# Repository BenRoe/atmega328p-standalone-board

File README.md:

# 328p-Standalone-TH

Development board for the Atmega328P with USB-C connector and only through hole components.  
It's very handy to flash the bootloader on many Atmega328P IC's.

## Features

- ISP 6/10 header for bootloader flashing (recommend [USBaspLoader](https://github.com/baerwolf/USBaspLoader))
- USB-C connector (if USBaspLoader bootloader is on the Atmega328P, you can flash the firmware via USB)
- ISP activity led (MISO Pin)
- Boot/Reset switch
- [ZIF](https://en.wikipedia.org/wiki/Zero_insertion_force) socket for easy MCU swap

- [Schematic](schematic.pdf)
- [BOM](http://htmlpreview.github.io/?https://github.com/BenRoe/atmega328p-standalone-board/blob/master/bom/ibom.html)
- [Gerber files](gerber/328p-standalone-rev1.0.zip) (ready to use)

## License

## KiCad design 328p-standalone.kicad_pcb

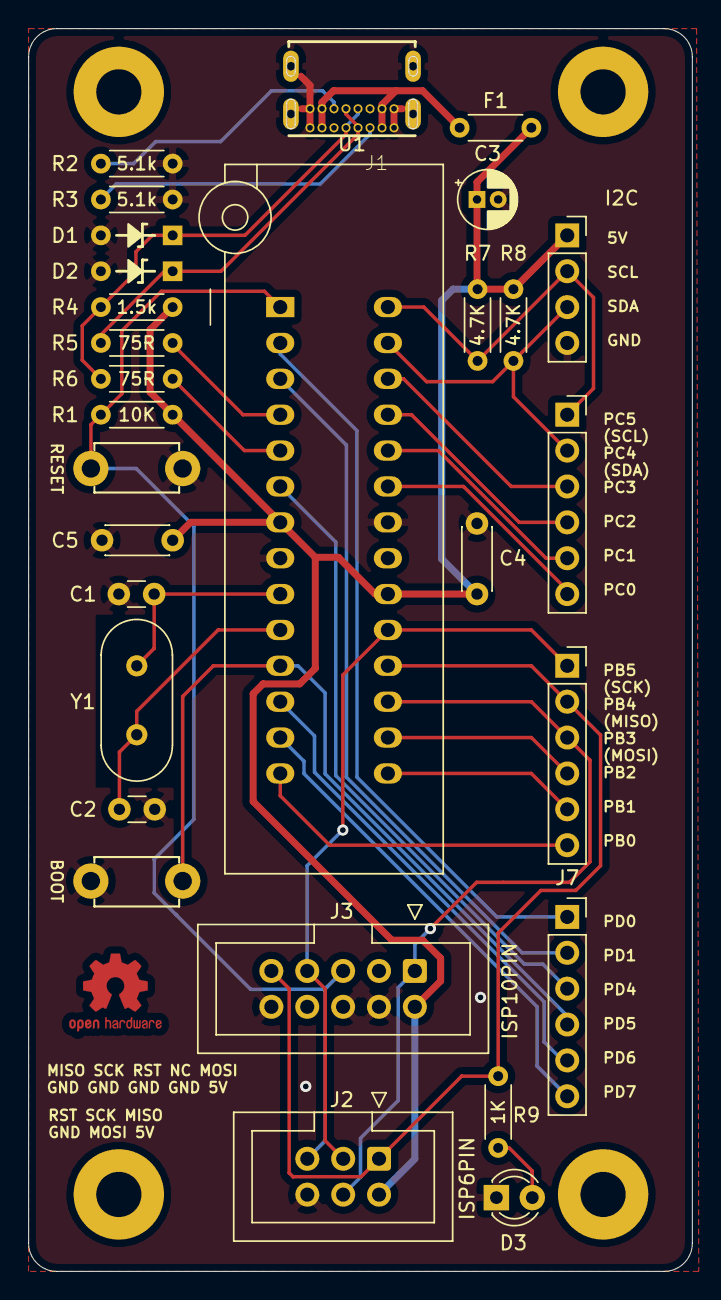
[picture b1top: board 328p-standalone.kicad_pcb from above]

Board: 2 copper layers, 47.0 x 88.0 mm, 33 parts (0 on the bottom side), 31 nets.

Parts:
C1, C2: 22pF; C_Disc_D3.0mm_W1.6mm_P2.50mm
C3: 4.7uF; CP_Radial_D4.0mm_P1.50mm
C4, C5: 100nF; C_Disc_D4.3mm_W1.9mm_P5.00mm
D1, D2: 3.6V; Diode-Zener-35_SOD27_P5.08mm_Horizontal
D3: LED; LED_D3.0mm
F1: 500mA; R_Axial_DIN0204_L3.6mm_D1.6mm_P5.08mm_Horizontal
H1, H2, H3, H4: MountingHole; MountingHole_3.2mm_M3_Pad
J1: USB4085-GF-A_REVA; GCT_USB4085-GF-A_REVA
J2: ISP6PIN; IDC-Header_2x03_P2.54mm_Vertical
J3: ISP10PIN; IDC-Header_2x05_P2.54mm_Vertical
J4: I2C; PinSocket_1x04_P2.54mm_Vertical
J5, J6, J7: Conn_01x06; PinSocket_1x06_P2.54mm_Vertical
R1: 10K; R_Axial_DIN0204_L3.6mm_D1.6mm_P5.08mm_Horizontal
R2, R3: 5.1k; R_Axial_DIN0204_L3.6mm_D1.6mm_P5.08mm_Horizontal
R4: 1.5k; R_Axial_DIN0204_L3.6mm_D1.6mm_P5.08mm_Horizontal
R5, R6: 75R; R_Axial_DIN0204_L3.6mm_D1.6mm_P5.08mm_Horizontal
R7, R8: 4.7K; R_Axial_DIN0204_L3.6mm_D1.6mm_P5.08mm_Horizontal
R9: 1K; R_Axial_DIN0204_L3.6mm_D1.6mm_P5.08mm_Horizontal
SW1: RESET; TACT_SWITCH_TVBP06
SW2: BOOT; TACT_SWITCH_TVBP06
U1: ATmega328P-PU; DIP_Socket-28_ZIF-228-3341_7.62mm-row-spacing
Y1: 16Mhz; Crystal_HC49-4H_Vertical

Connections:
+5V: C3.1, C4.1, C5.1, F1.2, J2.2, J3.2, J4.1, R1.2, R4.2, R7.2, R8.2, U1.7, U1.20
/PB0: J6.6, U1.14
/PB1: J6.5, U1.15
/PB2: J6.4, U1.16
/PC0: J5.6, U1.23
/PC1: J5.5, U1.24
/PC2: J5.4, U1.25
/PC3: J5.3, U1.26
/PD0: J7.1, U1.2
/PD1: J7.2, U1.3
/PD4: J7.3, U1.6
/PD5: J7.4, SW2.1, U1.11
/PD6: J7.5, U1.12
/PD7: J7.6, U1.13
GND: C1.1, C2.1, C3.2, C4.2, C5.2, D1.2, D2.2, D3.1, J1.A1, J1.A12, J1.B1, J1.B12, J1.P1, J1.P2, J1.P3, J1.P4, J2.6, J3.4, J3.6, J3.8, J3.10, J4.4, R2.2, R3.2, SW1.2, SW2.2, U1.8, U1.22
I2C_SCL: J4.2, J5.1, R7.1, U1.28
I2C_SDA: J4.3, J5.2, R8.1, U1.27
MISO: J2.1, J3.9, J6.2, R9.1, U1.18
MOSI: J2.4, J3.1, J6.3, U1.17
unnamed: C1.2, U1.9, Y1.1
unnamed: C2.2, U1.10, Y1.2
unnamed: D1.1, J1.A7, J1.B7, R4.1, R6.2
unnamed: D2.1, J1.A6, J1.B6, R5.2
unnamed: D3.2, R9.2
unnamed: F1.1, J1.A4, J1.A9, J1.B4, J1.B9
unnamed: J1.A5, R3.1
unnamed: J1.B5, R2.1
RST: J2.5, J3.5, R1.1, SW1.1, U1.1
SCK: J2.3, J3.7, J6.1, U1.19
USB_D+: R5.1, U1.4
USB_D-: R6.1, U1.5

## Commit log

2020-08-27 add gitignore file for kicad
2020-11-10 add readme and img
2020-11-10 add ibom
2020-11-10 add kicad and gerber files
2020-11-10 add schematic link to readme
2020-11-10 add license to readme

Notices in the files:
README.md:
License:
[https://mirrors.creativecommons.org/presskit/buttons/88x31/svg/by-nc-sa.svg](http://creativecommons.org/licenses/by-nc-sa/4.0/)
